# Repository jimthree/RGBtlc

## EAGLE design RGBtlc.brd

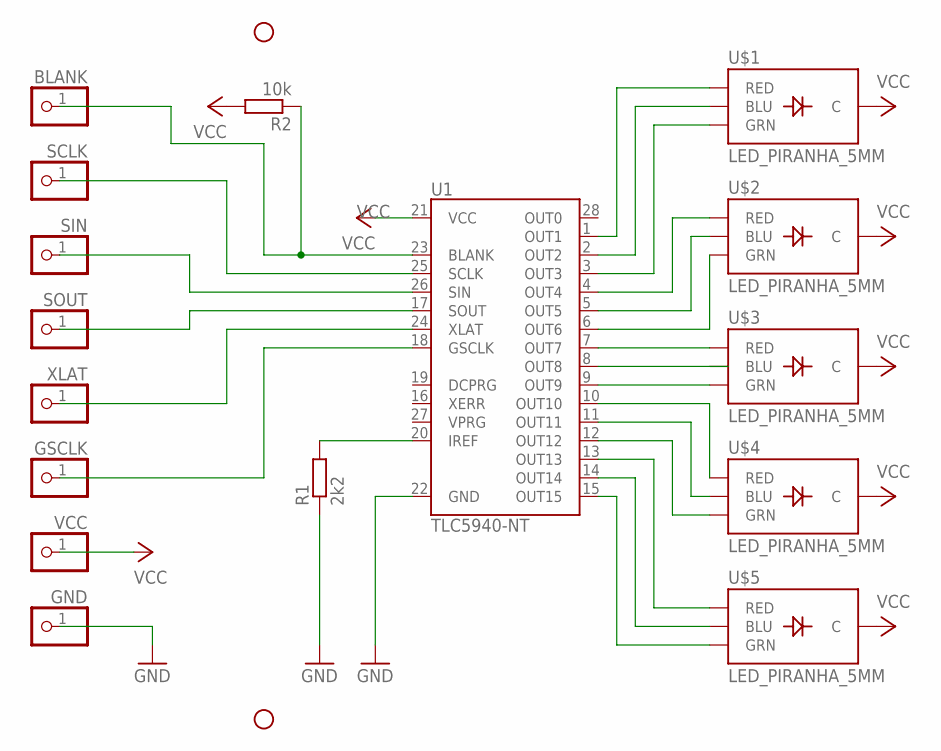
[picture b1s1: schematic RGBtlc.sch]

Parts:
BLANK: PINHD-1X1; 1X01
GND: PINHD-1X1; 1X01
GSCLK: PINHD-1X1; 1X01
JP1, JP4: STAND-OFF
R1: 2k2; 0207/7
R2: 10k; 0207/7
SCLK: PINHD-1X1; 1X01
SIN: PINHD-1X1; 1X01
SOUT: PINHD-1X1; 1X01
U1: TLC5940-NT; DIL28-3
U$1, U$2, U$3, U$4, U$5: LED_PIRANHA_5MM
VCC: PINHD-1X1; 1X01
XLAT: PINHD-1X1; 1X01

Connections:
GND: GND.1, R1.1, U1.22 (GND)
unnamed: U1.15 (OUT15), U$5.G (GRN)
unnamed: U1.14 (OUT14), U$5.B (BLU)
unnamed: U1.13 (OUT13), U$5.R (RED)
unnamed: U1.8 (OUT8), U$3.B (BLU)
unnamed: U1.12 (OUT12), U$4.G (GRN)
unnamed: U1.11 (OUT11), U$4.B (BLU)
unnamed: U1.10 (OUT10), U$4.R (RED)
unnamed: U1.9 (OUT9), U$3.G (GRN)
unnamed: BLANK.1, R2.1, U1.23 (BLANK)
unnamed: U1.7 (OUT7), U$3.R (RED)
unnamed: U1.6 (OUT6), U$2.G (GRN)
unnamed: U1.5 (OUT5), U$2.B (BLU)
unnamed: U1.4 (OUT4), U$2.R (RED)
unnamed: U1.3 (OUT3), U$1.G (GRN)
unnamed: U1.2 (OUT2), U$1.B (BLU)
unnamed: U1.1 (OUT1), U$1.R (RED)
unnamed: SCLK.1, U1.25 (SCLK)
unnamed: SIN.1, U1.26 (SIN)
unnamed: U1.24 (XLAT), XLAT.1
unnamed: GSCLK.1, U1.18 (GSCLK)
unnamed: SOUT.1, U1.17 (SOUT)
unnamed: R1.2, U1.20 (IREF)
VCC: R2.2, U1.21 (VCC), U$1.- (C), U$2.- (C), U$3.- (C), U$4.- (C), U$5.- (C), VCC.1

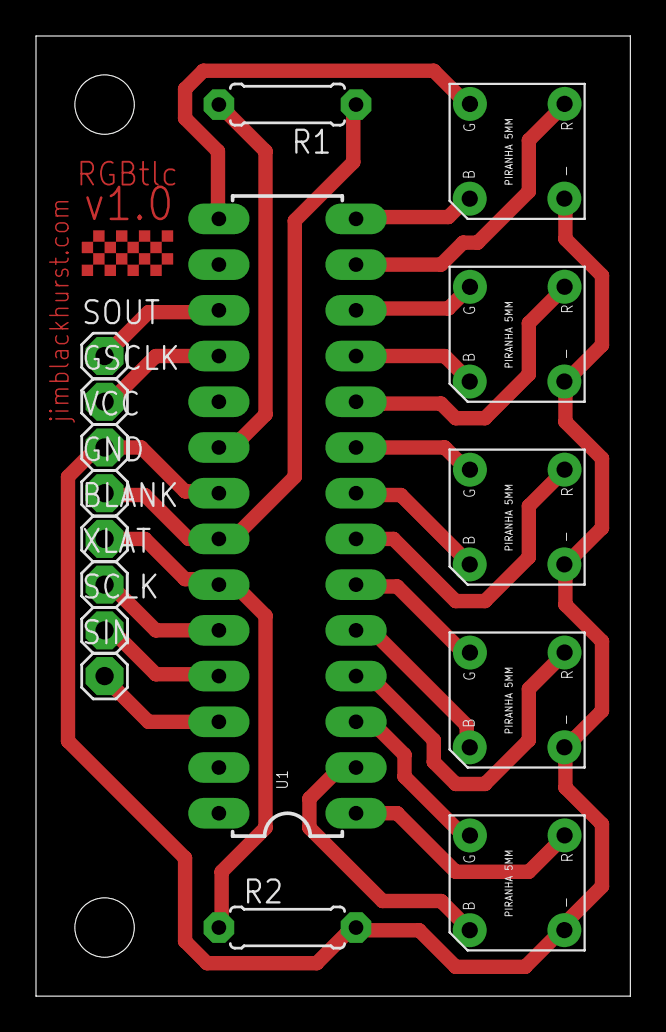
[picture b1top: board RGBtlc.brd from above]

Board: 2 copper layers, 33.0 x 53.3 mm, 18 parts (0 on the bottom side), 24 nets.

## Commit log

2012-05-01 initial commit ignore all *.b#? and *.s#? files
2012-05-28 V2, now with daisy chain ports

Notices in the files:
parts and their libraries:
SparkFun-DigitalIC: Licensing: CC v3.0 Share-Alike You are welcome to use this library for commercial purposes.
